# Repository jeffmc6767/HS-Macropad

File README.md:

This is my custom Hotswappable Macropad:
-

This macropad has 9 keys(3x3), 2 rotary encoders and is controlled through a Seeduino Xiao RP2040. 

Some images(to come): 

Reminding myself where the parts are: 
https://kailhswitch.net/products/kailh-hot-swap-pcb-socket-diy-mechanical-keyboard-switches?srsltid=AfmBOoou1a8ZSbBuGYF_AU1epghGp4K7qxQYPx9-Ia8cNmjXQ4em4Oea

BOM:
**THIS IS IN UNIT PRICE!!**
1 seeduino Xiao $9
11 1n4148 Diodes 89¢
9 Kailh hot swap sockets $1.25
9 Gateron KS-3X10 $14.99 (pack of 35)
2 EC11 rotary encoders(PEC11R-4225F-N0024-ND) $3.5
1 PCB(pack of 5) $11 (global shipping)
1 soldering iron kit $25
PLA matte black $5

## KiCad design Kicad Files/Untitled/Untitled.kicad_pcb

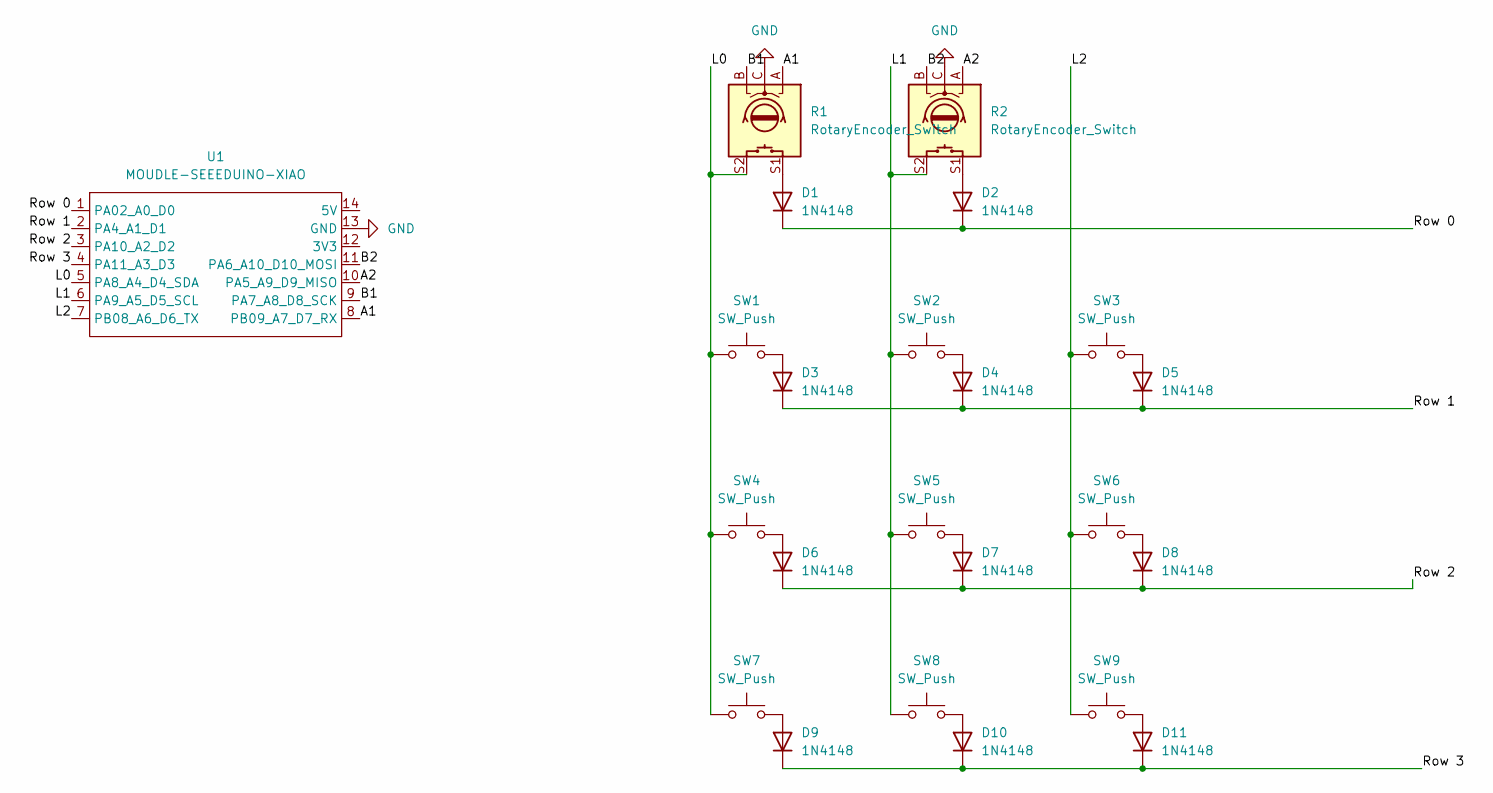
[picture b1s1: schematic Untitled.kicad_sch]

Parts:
D1, D2, D3, D4, D5, D6, D7, D8, D9, D10, D11: 1N4148; D_DO-35_SOD27_P7.62mm_Horizontal
R1, R2: RotaryEncoder_Switch; RotaryEncoder_Alps_EC11E-Switch_Vertical_H20mm
SW1, SW2, SW3, SW4, SW5, SW6, SW7, SW8, SW9: SW_Push; SW_Hotswap_Kailh_Choc_V1V2_1.00u
U1: MOUDLE-SEEEDUINO-XIAO; XIAO-Generic-Hybrid-14P-2.54-21X17.8MM

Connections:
/A1: R1.A, U1.8 (PB09_A7_D7_RX)
/A2: R2.A, U1.10 (PA5_A9_D9_MISO)
/B1: R1.B, U1.9 (PA7_A8_D8_SCK)
/B2: R2.B, U1.11 (PA6_A10_D10_MOSI)
/L0: R1.S2, SW1.1, SW4.1, SW7.1, U1.5 (PA8_A4_D4_SDA)
/L1: R2.S2, SW2.1, SW5.1, SW8.1, U1.6 (PA9_A5_D5_SCL)
/L2: SW3.1, SW6.1, SW9.1, U1.7 (PB08_A6_D6_TX)
/Row 0: D1.1 (K), D2.1 (K), U1.1 (PA02_A0_D0)
/Row 1: D3.1 (K), D4.1 (K), D5.1 (K), U1.2 (PA4_A1_D1)
/Row 2: D6.1 (K), D7.1 (K), D8.1 (K), U1.3 (PA10_A2_D2)
/Row 3: D9.1 (K), D10.1 (K), D11.1 (K), U1.4 (PA11_A3_D3)
GND: R1.C, R2.C, U1.13 (GND)
unnamed: D1.2 (A), R1.S1
unnamed: D2.2 (A), R2.S1
unnamed: D3.2 (A), SW1.2
unnamed: D4.2 (A), SW2.2
unnamed: D5.2 (A), SW3.2
unnamed: D6.2 (A), SW4.2
unnamed: D7.2 (A), SW5.2
unnamed: D8.2 (A), SW6.2
unnamed: D9.2 (A), SW7.2
unnamed: D10.2 (A), SW8.2
unnamed: D11.2 (A), SW9.2

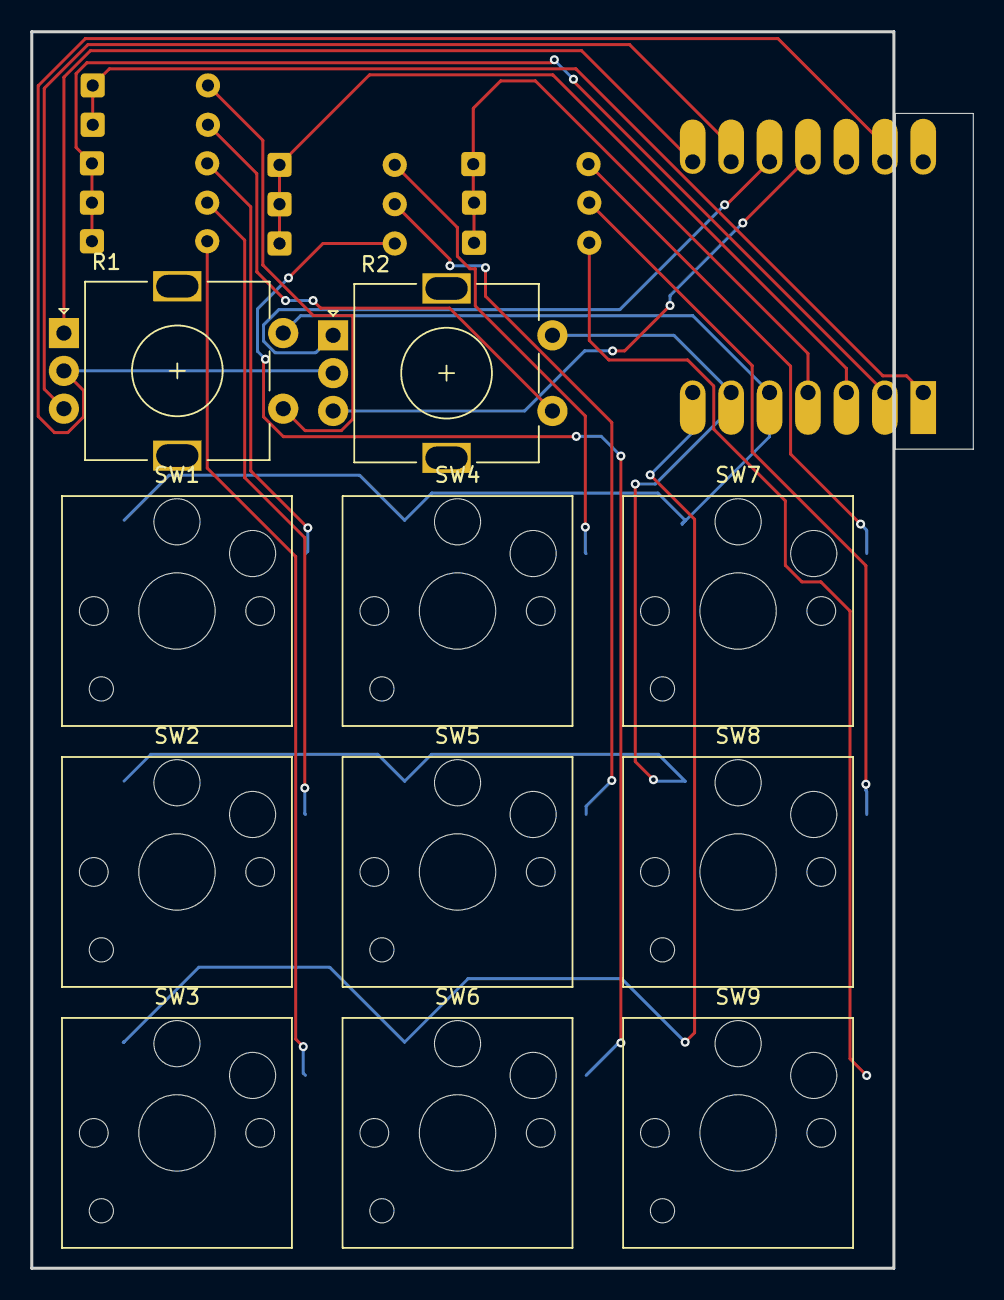
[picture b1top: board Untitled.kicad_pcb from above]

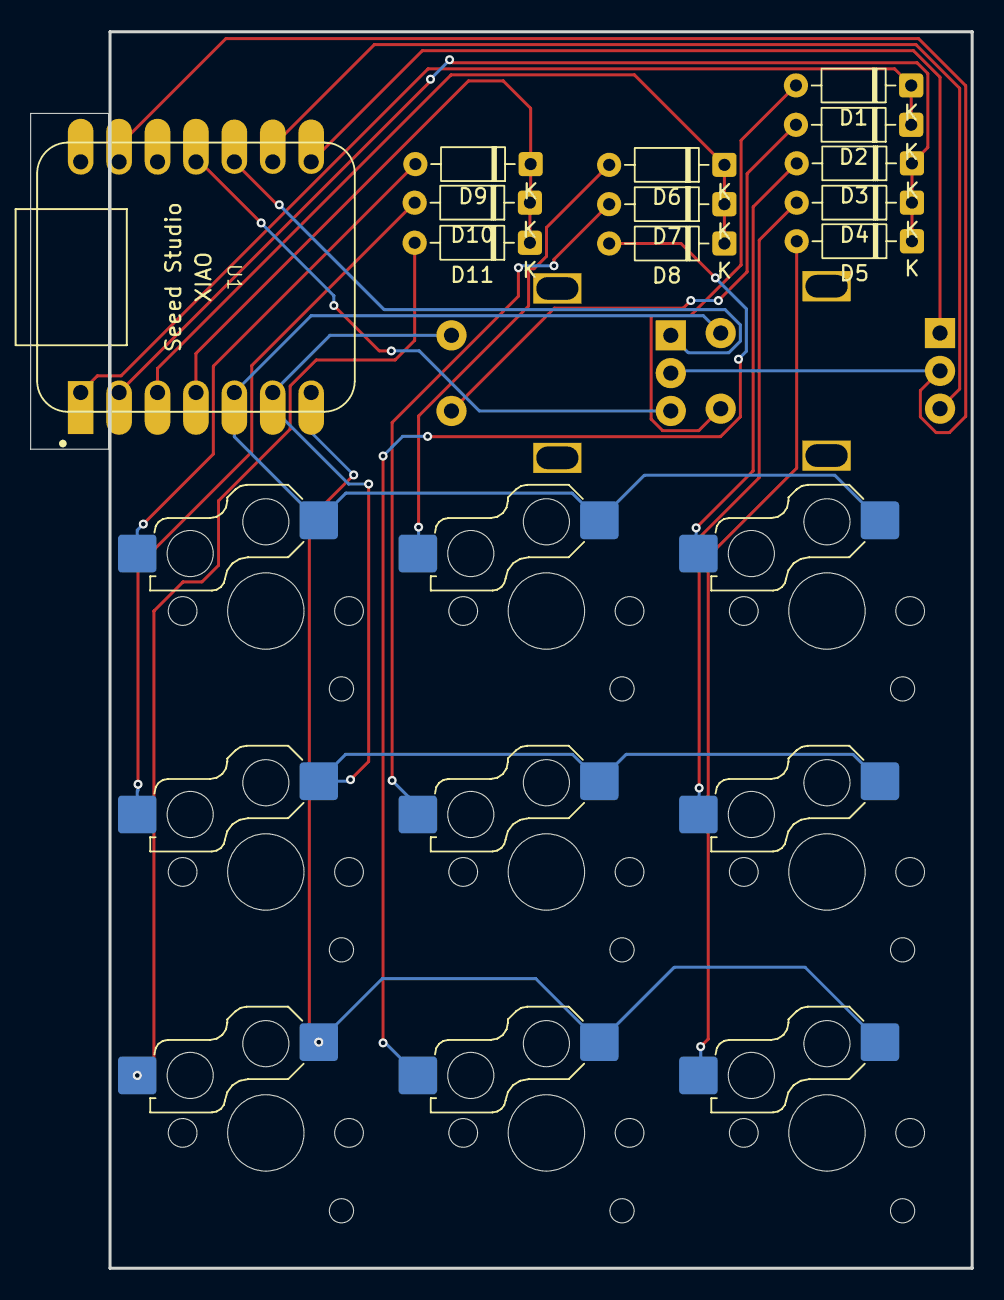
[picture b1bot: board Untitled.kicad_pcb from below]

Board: 2 copper layers, 62.2 x 81.8 mm, 23 parts (12 on the bottom side), 23 nets.
